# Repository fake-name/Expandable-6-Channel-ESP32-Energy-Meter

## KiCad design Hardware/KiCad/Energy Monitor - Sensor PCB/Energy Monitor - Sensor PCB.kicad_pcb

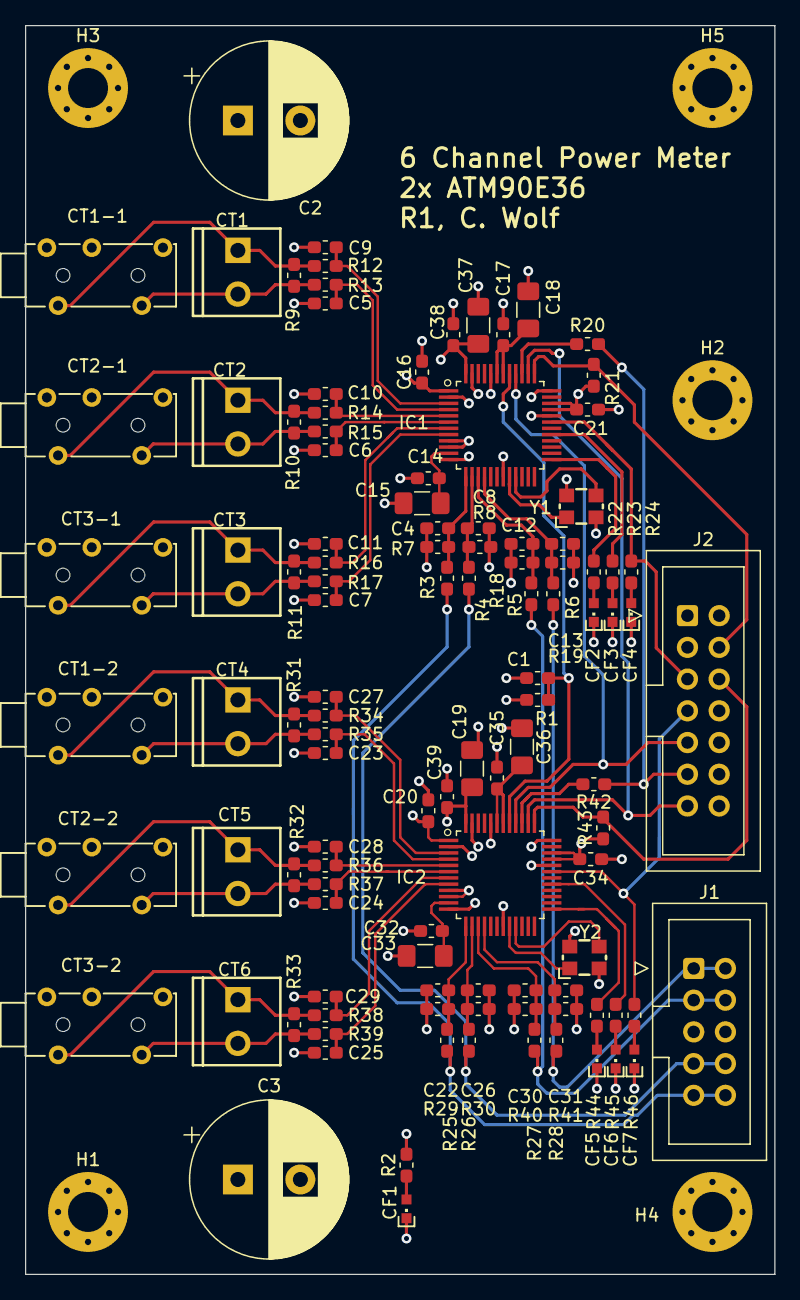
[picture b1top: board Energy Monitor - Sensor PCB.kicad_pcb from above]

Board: 4 copper layers, 60.0 x 100.0 mm, 115 parts (0 on the bottom side), 67 nets.

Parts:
C1, C14, C16, C17, C20, C21, C32, C34, C35, C38, C39: 0.1uF; C_0603_1608Metric_Pad1.05x0.95mm_HandSolder
C2, C3: CP1; CP_Radial_D12.5mm_P5.00mm
C4, C8, C12, C13, C22, C26, C30, C31: 18nF; C_0603_1608Metric_Pad1.05x0.95mm_HandSolder
C5, C6, C7, C9, C10, C11, C23, C24, C25, C27, C28, C29: 0.33uF; C_0603_1608Metric_Pad1.05x0.95mm_HandSolder
C15, C18, C19, C33, C36, C37: 10uF; C_1206_3216Metric_Pad1.42x1.75mm_HandSolder
CF1, CF2, CF3, CF4, CF5, CF6, CF7: BLU; CHIPLED_0603
CT1, CT2, CT3, CT4, CT5, CT6: CONN_023.5MM; SCREWTERMINAL-3.5MM-2
CT1-1, CT1-2, CT2-1, CT2-2, CT3-1, CT3-2: SJ2-35813B-SMT-TR; PJ-3270
H1, H2, H3, H4, H5: MountingHole; MountingHole_3.2mm_M3_Pad_Via
IC1, IC2: ATM90E36; QFP50P900X900X120-48
J1: Conn_02x05_Odd_Even; IDC-Header_2x05_P2.54mm_Vertical
J2: Conn_02x07_Odd_Even; IDC-Header_2x07_P2.54mm_Vertical
R1, R21, R43: 10K; R_0603_1608Metric_Pad1.05x0.95mm_HandSolder
R2: 1k; R_0603_1608Metric_Pad1.05x0.95mm_HandSolder
R3, R4, R5, R6, R25, R26, R27, R28: 20K; R_0603_1608Metric_Pad1.05x0.95mm_HandSolder
R7, R8, R18, R19, R22, R23, R24, R29, R30, R40, R41, R44, R45, R46: 1K; R_0603_1608Metric_Pad1.05x0.95mm_HandSolder
R9, R10, R11, R31, R32, R33: 22R; R_0603_1608Metric_Pad1.05x0.95mm_HandSolder
R12, R13, R14, R15, R16, R17, R20, R34, R35, R36, R37, R38, R39, R42: 100R; R_0603_1608Metric_Pad1.05x0.95mm_HandSolder
Y1, Y2: 16.384MHz; CRYSTAL-SMD-3.2X2.5MM

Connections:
+3V3: C2.1, C3.1, C16.1, C19.1, C20.1, C21.1, C34.1, C37.1, C38.1, C39.1, IC1.1, IC1.33, IC1.34, IC1.48, IC2.1, IC2.33, IC2.34, IC2.48, J2.1, J2.3, R1.1, R2.2, R21.1, R43.1
/meter_1/1.8VDD: C17.1, C18.1, IC1.42, IC1.43
/meter_1/I1N: C5.1, IC1.4, R13.2
/meter_1/I1P: C9.1, IC1.3, R12.2
/meter_1/I2N: C6.1, IC1.6, R15.2
/meter_1/I2P: C10.1, IC1.5, R14.2
/meter_1/I3N: C7.1, IC1.8, R17.2
/meter_1/I3P: C11.1, IC1.7, R16.2
/meter_1/IRQ1: IC1.31, J2.5, R24.1
/meter_1/SCLK: IC1.38, IC2.38, J2.13
/meter_1/SDI: IC1.40, IC2.40, J2.9
/meter_1/SDO: J2.11, R20.1, R42.1
/meter_1/V1N: J1.7, J1.8, R4.2, R26.2
/meter_1/V1P: J1.9, J1.10, R3.2, R25.2
/meter_1/V2N: J1.1, J1.2, R6.2, R28.2
/meter_1/V2P: J1.3, J1.4, R5.2, R27.2
/meter_1/~CS: IC1.37, J2.4, R21.2
/meter_1/~RESET: C1.1, IC1.41, IC2.41, R1.2
/meter_2/1.8VDD: C35.1, C36.1, IC2.42, IC2.43
/meter_2/I1N: C23.1, IC2.4, R35.2
/meter_2/I1P: C27.1, IC2.3, R34.2
/meter_2/I2N: C24.1, IC2.6, R37.2
/meter_2/I2P: C28.1, IC2.5, R36.2
/meter_2/I3N: C25.1, IC2.8, R39.2
/meter_2/I3P: C29.1, IC2.7, R38.2
/meter_2/IRQ1: IC2.31, J2.7, R46.1
/meter_2/~CS: IC2.37, J2.6, R43.2
GND: C1.2, C2.2, C3.2, C4.2, C5.2, C6.2, C7.2, C8.2, C9.2, C10.2, C11.2, C12.2, C13.2, C14.2, C15.2, C16.2, C17.2, C18.2, C19.2, C20.2, C21.2, C22.2, C23.2, C24.2, C25.2, C26.2, C27.2, C28.2, C29.2, C30.2, C31.2, C32.2, C33.2, C34.2, C35.2, C36.2, C37.2, C38.2, C39.2, CF1.C, CF2.C, CF3.C, CF4.C, CF5.C, CF6.C, CF7.C, IC1.2, IC1.9, IC1.10, IC1.12, IC1.19, IC1.32, IC1.36, IC1.44, IC1.47, IC2.2, IC2.9, IC2.10, IC2.12, IC2.19, IC2.32, IC2.36, IC2.44, IC2.47, J2.8, J2.10, J2.12, J2.14, R7.1, R8.1, R18.1, R19.1, R29.1, R30.1, R40.1, R41.1, Y1.2, Y1.4, Y2.2, Y2.4
unnamed: C4.1, IC1.13, R3.1, R7.2
unnamed: C8.1, IC1.14, R4.1, R8.2
unnamed: C12.1, IC1.15, R5.1, R18.2
unnamed: C13.1, IC1.16, R6.1, R19.2
unnamed: C14.1, C15.1, IC1.11
unnamed: C22.1, IC2.13, R25.1, R29.2
unnamed: C26.1, IC2.14, R26.1, R30.2
unnamed: C30.1, IC2.15, R27.1, R40.2
unnamed: C31.1, IC2.16, R28.1, R41.2
unnamed: C32.1, C33.1, IC2.11
unnamed: CF1.A, R2.1
unnamed: CF2.A, R22.2
unnamed: CF3.A, R23.2
unnamed: CF4.A, R24.2
unnamed: CF5.A, R44.2
unnamed: CF6.A, R45.2
unnamed: CF7.A, R46.2
unnamed: CT1.2, CT1-1.2, R9.1, R13.1
unnamed: CT1.1, CT1-1.3, R9.2, R12.1
unnamed: CT1-2.2, CT4.2, R31.1, R35.1
unnamed: CT1-2.3, CT4.1, R31.2, R34.1
unnamed: CT2.2, CT2-1.2, R10.1, R15.1
unnamed: CT2.1, CT2-1.3, R10.2, R14.1
unnamed: CT2-2.2, CT5.2, R32.1, R37.1
unnamed: CT2-2.3, CT5.1, R32.2, R36.1
unnamed: CT3.2, CT3-1.2, R11.1, R17.1
unnamed: CT3.1, CT3-1.3, R11.2, R16.1
unnamed: CT3-2.2, CT6.2, R33.1, R39.1
unnamed: CT3-2.3, CT6.1, R33.2, R38.1
unnamed: IC1.20, Y1.1
unnamed: IC1.21, Y1.3
unnamed: IC1.25, R22.1
unnamed: IC1.29, R23.1
unnamed: IC1.39, R20.2
unnamed: IC2.20, Y2.1
unnamed: IC2.21, Y2.3
unnamed: IC2.25, R44.1
unnamed: IC2.29, R45.1
unnamed: IC2.39, R42.2

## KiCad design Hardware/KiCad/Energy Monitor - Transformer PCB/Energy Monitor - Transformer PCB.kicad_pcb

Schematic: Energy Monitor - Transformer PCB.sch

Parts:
C1, C2, C3: CP1; CP_Radial_D12.5mm_P5.00mm
D1, D2, D3, D4: D; D_DO-41_SOD81_P12.70mm_Horizontal
D5: LED; LED_D5.0mm_Clear
H1, H2, H3, H4: MountingHole; MountingHole_3.2mm_M3_Pad_Via
J1, J2, J3: Conn_01x02; WE 691411410002 - 2 Pin Wire-To-Board Terminal Block
J4, J5, J6, J7, J8, J9, J10, J11: Conn_02x05_Odd_Even; IDC-Header_2x05_P2.54mm_Vertical
R1: 1K; R_Axial_DIN0309_L9.0mm_D3.2mm_P15.24mm_Horizontal
T1, T2: EI30-15.5; EI30-15.5-TH
T3: AHI050; AHI050-TH

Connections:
+9V: C1.1, C2.1, C3.1, D1.1 (K), D2.1 (K), J10.1, J10.3, J10.5, J10.7, J11.1, J11.3, J11.5, J11.7, R1.1
GND: C1.2, C2.2, C3.2, D3.2 (A), D4.2 (A), D5.1 (K), J10.4, J10.6, J10.8, J10.10, J11.4, J11.6, J11.8, J11.10
unnamed: D1.2 (A), D4.1 (K), T3.6, T3.8
unnamed: D2.2 (A), D3.1 (K), T3.5, T3.7
unnamed: D5.2 (A), R1.2
unnamed: J1.1, T1.1
unnamed: J1.2, T1.5
unnamed: J2.1, T2.1
unnamed: J2.2, T2.5
unnamed: J3.1, T3.1, T3.3
unnamed: J3.2, T3.2, T3.4
unnamed: J4.1, J4.2, J5.1, J5.2, J6.1, J6.2, J7.1, J7.2, J8.1, J8.2, J9.1, J9.2, T1.9
unnamed: J4.3, J4.4, J5.3, J5.4, J6.3, J6.4, J7.3, J7.4, J8.3, J8.4, J9.3, J9.4, T1.7
unnamed: J4.7, J4.8, J5.7, J5.8, J6.7, J6.8, J7.7, J7.8, J8.7, J8.8, J9.7, J9.8, T2.9
unnamed: J4.9, J4.10, J5.9, J5.10, J6.9, J6.10, J7.9, J7.10, J8.9, J8.10, J9.9, J9.10, T2.7

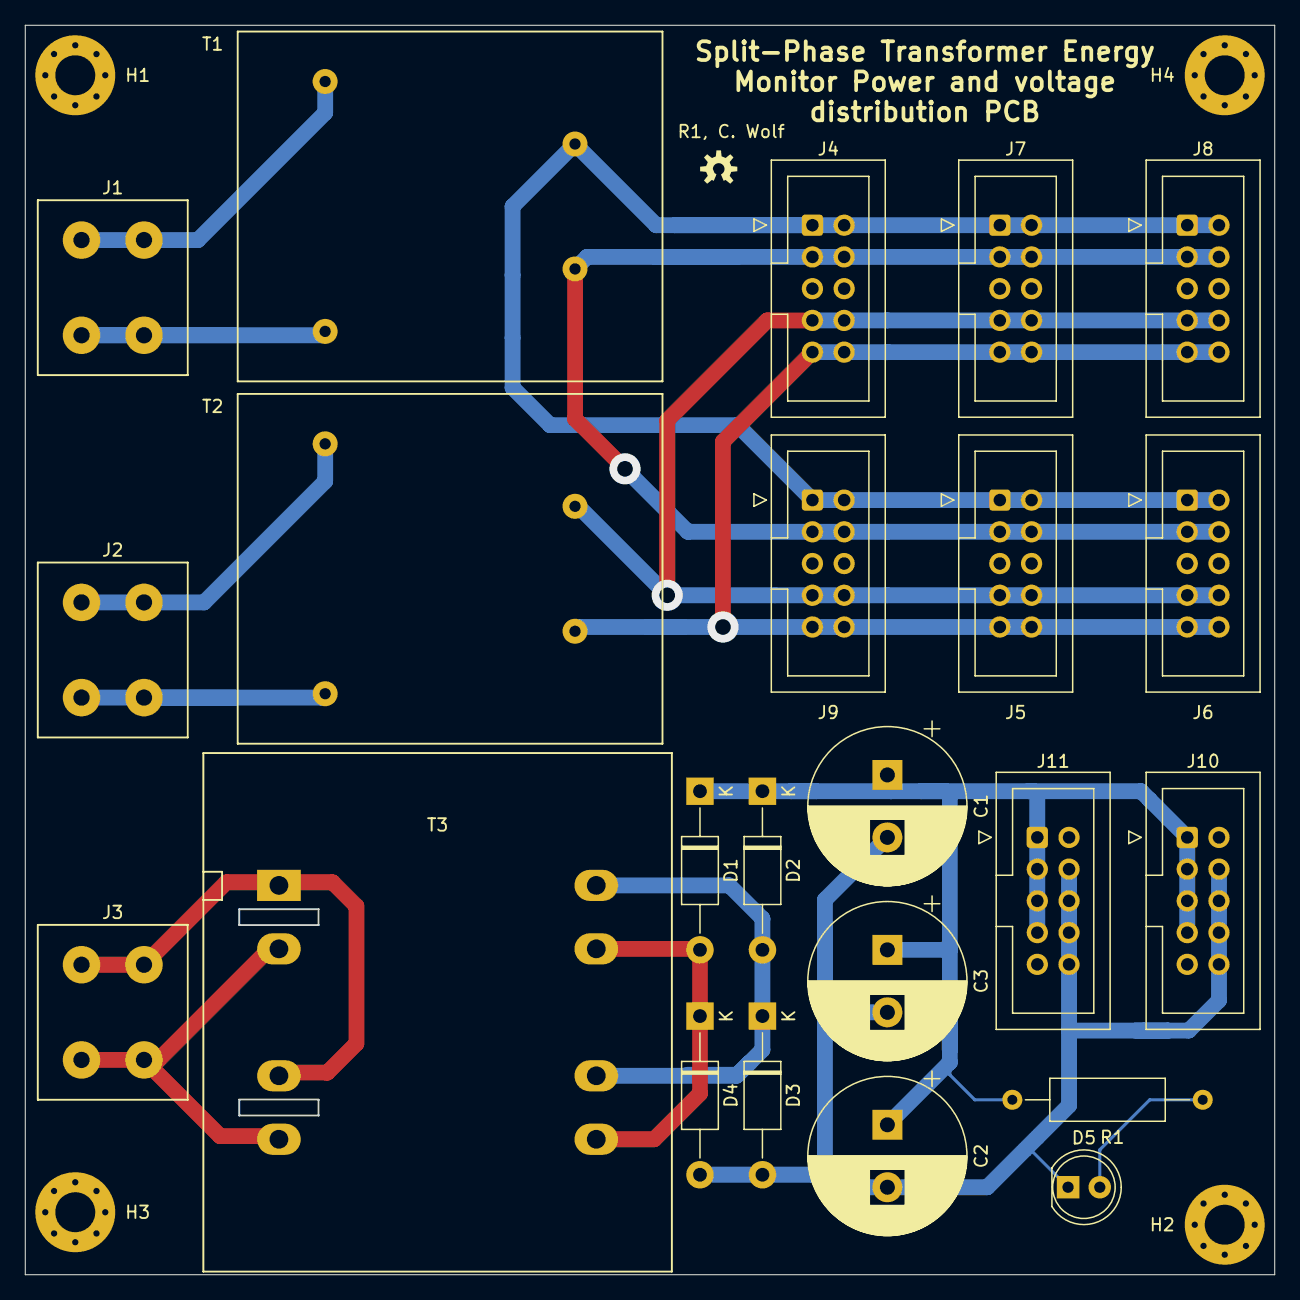
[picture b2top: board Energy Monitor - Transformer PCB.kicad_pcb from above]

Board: 2 copper layers, 99.9 x 99.9 mm, 27 parts (0 on the bottom side), 15 nets.

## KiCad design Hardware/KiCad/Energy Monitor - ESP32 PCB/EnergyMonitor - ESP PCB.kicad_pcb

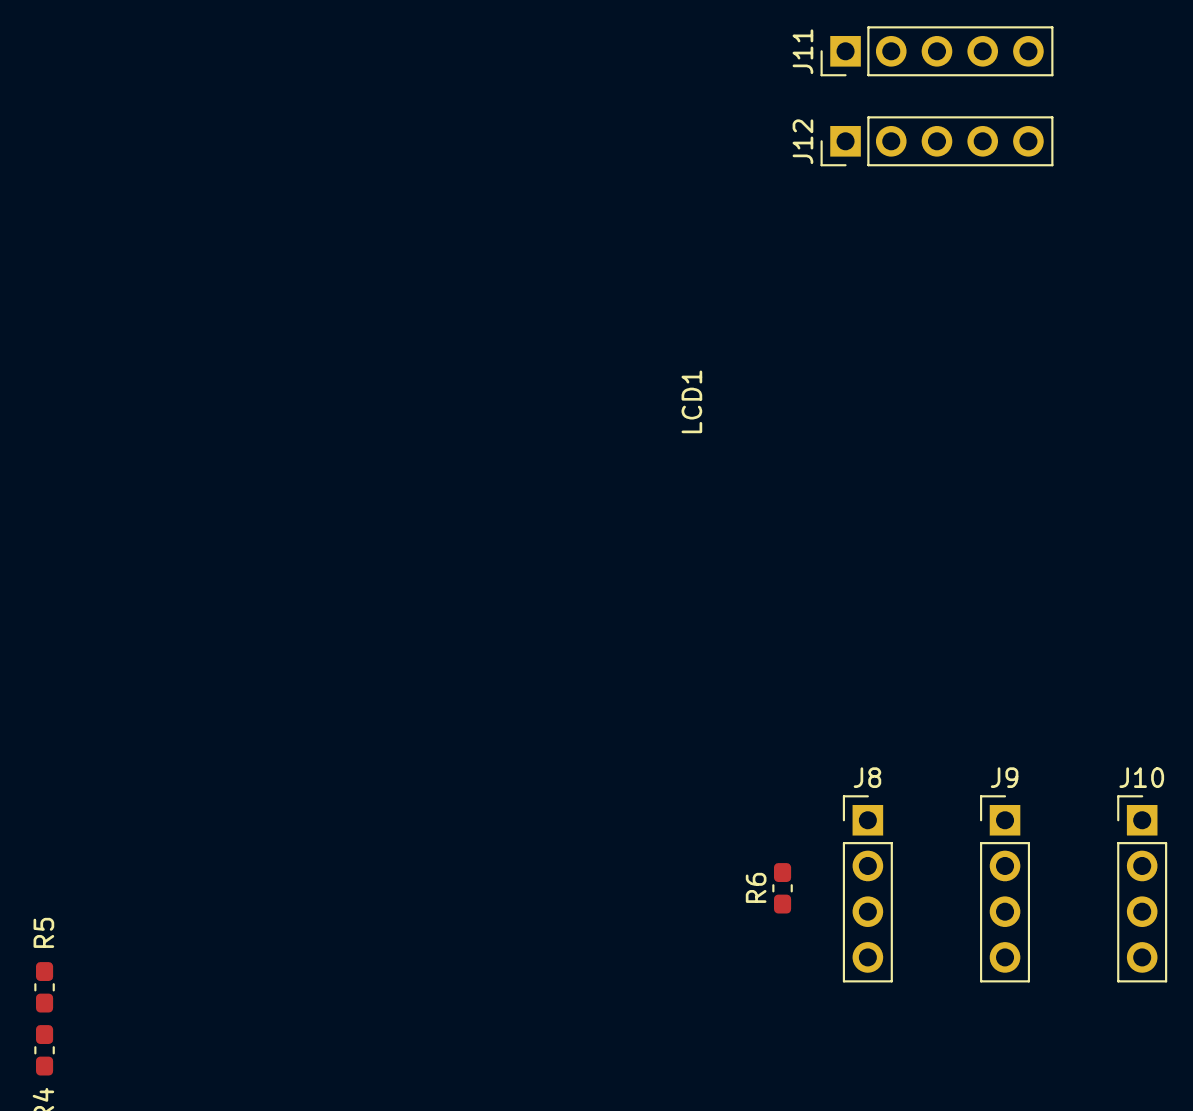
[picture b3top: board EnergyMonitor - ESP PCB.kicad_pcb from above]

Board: 4 copper layers, 9 parts (0 on the bottom side), 6 nets, no tracks yet.

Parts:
J8, J9, J10: Conn_01x04; PinHeader_1x04_P2.54mm_Vertical
J11, J12: Conn_01x05; PinHeader_1x05_P2.54mm_Vertical
LCD1: 0.96; 12864-DISP-I2C
R4, R5: 2.2K; R_0603_1608Metric_Pad1.05x0.95mm_HandSolder
R6: 10K; R_0603_1608Metric_Pad1.05x0.95mm_HandSolder

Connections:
+3V3: J8.3, J9.3, J10.3, J11.2, J12.2, R4.1, R5.1, R6.1
+5V: J8.4, J9.4, J10.4, J11.1, J12.1
GND: J8.1, J9.1, J10.1, J11.5, J12.5
unnamed: J8.2, J9.2, J10.2, R6.2
unnamed: J11.3, J12.3, R5.2
unnamed: J11.4, J12.4, R4.2

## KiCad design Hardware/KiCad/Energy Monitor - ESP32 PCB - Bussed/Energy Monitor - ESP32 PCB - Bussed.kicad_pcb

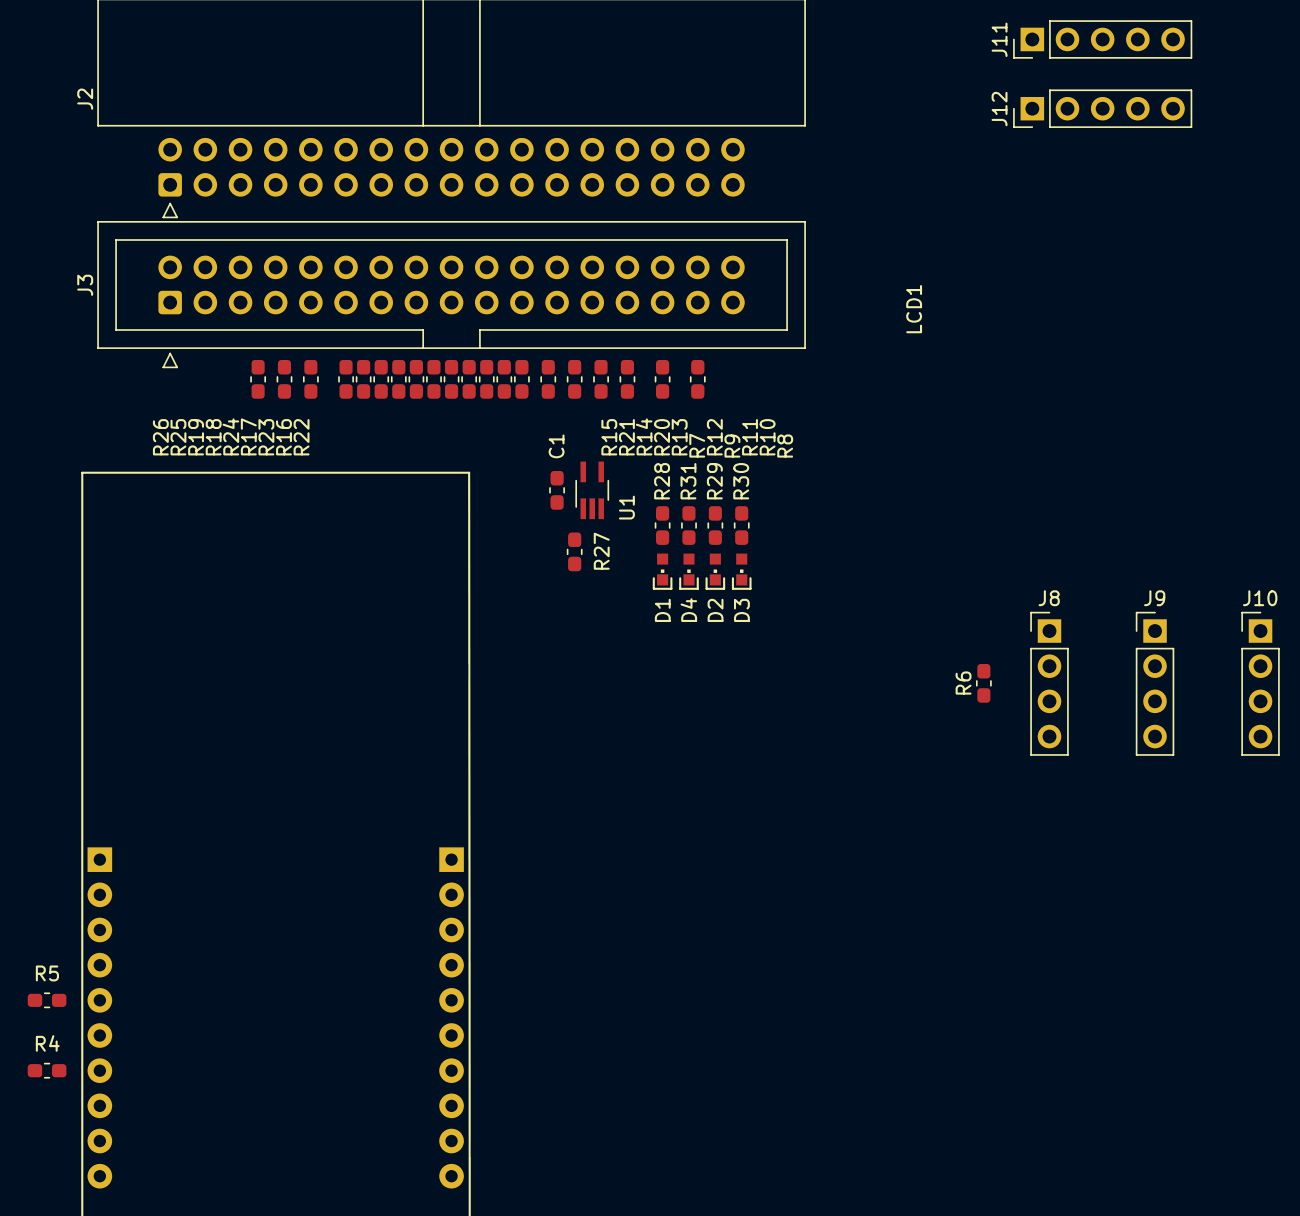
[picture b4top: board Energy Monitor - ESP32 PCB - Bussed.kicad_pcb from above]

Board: 4 copper layers, 43 parts (0 on the bottom side), 32 nets, no tracks yet.

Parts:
C1: 0.1 uF; C_0603_1608Metric_Pad1.05x0.95mm_HandSolder
D1, D2, D3, D4: LED; CHIPLED_0603
J2: Conn_02x17_Odd_Even; IDC-Header_2x17_P2.54mm_Horizontal
J3: Conn_02x17_Odd_Even; IDC-Header_2x17_P2.54mm_Vertical
J8, J9, J10: Conn_01x04; PinHeader_1x04_P2.54mm_Vertical
J11, J12: Conn_01x05; PinHeader_1x05_P2.54mm_Vertical
LCD1: 0.96; 12864-DISP-I2C
R4, R5: 2.2K; R_0603_1608Metric_Pad1.05x0.95mm_HandSolder
R6, R27: 10K; R_0603_1608Metric_Pad1.05x0.95mm_HandSolder
R7, R9, R12: 660R; R_0603_1608Metric_Pad1.05x0.95mm_HandSolder
R8, R10, R11: 49.9K; R_0603_1608Metric_Pad1.05x0.95mm_HandSolder
R13, R14, R15, R16, R17, R18, R19, R20, R21, R22, R23, R24, R25, R26: 100R; R_0603_1608Metric_Pad1.05x0.95mm_HandSolder
R28, R29, R30, R31: 1K; R_0603_1608Metric_Pad1.05x0.95mm_HandSolder
U1: 74LVC1G04; SOT-353_SC-70-5_Handsoldering
U2: ESP32-POE Module; ESP32-POE

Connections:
+3V3: C1.1, J2.1, J2.3, J2.5, J2.7, J3.1, J3.3, J3.5, J3.7, J8.3, J9.3, J10.3, J11.2, J12.2, R4.1, R5.1, R6.1, R7.1, R9.1, R28.1, R31.1, U1.5
+5V: J2.2, J2.4, J2.6, J3.2, J3.4, J3.6, J8.4, J9.4, J10.4, J11.1, J12.1, R30.1, U2.1
/ESP1/IRQ_1: J2.23, J3.23, R7.2
/ESP1/IRQ_2: J2.25, J3.25, R9.2
/ESP1/MISO: J2.29, J3.29, R10.1, U2.13
/ESP1/MOSI: J2.27, J3.27, R11.1, U2.18
/ESP1/RESET: J2.22, J3.22, R12.1
/ESP1/SCL: J11.3, J12.3, R5.2, U2.5
/ESP1/SCLK: J2.31, J3.31, R8.1, U2.19
/ESP1/SDA: J11.4, J12.4, R4.2, U2.7
/ESP1/~CS_1: J2.8, J3.8, R26.2
/ESP1/~CS_2: J2.9, J3.9, R19.2
/ESP1/~CS_3: J2.10, J3.10, R25.2
/ESP1/~CS_4: J2.11, J3.11, R18.2
/ESP1/~CS_5: J2.12, J3.12, R24.2
/ESP1/~CS_6: J2.13, J3.13, R17.2
/ESP1/~CS_7: J2.14, J3.14, R23.2
/ESP1/~CS_8: J2.15, J3.15, R16.2
/ESP1/~CS_9: J2.16, J3.16, R22.2
/ESP1/~CS_10: J2.17, J3.17, R15.2
/ESP1/~CS_11: J2.18, J3.18, R21.2
/ESP1/~CS_12: J2.19, J3.19, R14.2
/ESP1/~CS_13: J2.20, J3.20, R20.2
/ESP1/~CS_14: J2.21, J3.21, R13.2
GND: C1.2, D2.1, D3.1, D4.1, J2.24, J2.26, J2.28, J2.30, J2.32, J2.33, J2.34, J3.24, J3.26, J3.28, J3.30, J3.32, J3.33, J3.34, J8.1, J9.1, J10.1, J11.5, J12.5, R8.2, R10.2, R11.2, R27.2, U1.3, U2.3
unnamed: D1.2, R28.2
unnamed: D2.2, R29.2
unnamed: D3.2, R30.2
unnamed: D4.2, R31.2
unnamed: J8.2, J9.2, J10.2, R6.2, U2.15
unnamed: R12.2, R29.1, U1.4
unnamed: R27.1, U1.2

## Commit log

2020-08-23 Convert to kicad.
2020-08-23 Make the schematic not terrible.
2020-08-23 Working on layout.
2020-08-24 Minor footprint cleanup.
2020-08-24 Project cleanup. Kicad has too many garbage files it sprays everywhere.
2020-08-25 Transformer PCB.
2020-08-25 Interface board.
2020-08-26 This seems to be getting progressively more complicated. Library cleanup, moved everything to my system library.
2020-08-29 Updates! I keep adding features.
2020-08-30 Progress!
2020-08-30 Bus-based board variant.
2020-08-31 Common-bus variant of the power monitor.
2020-08-31 MOAR.
2020-09-04 Blerp.
2020-09-06 Switch to a better jack.
